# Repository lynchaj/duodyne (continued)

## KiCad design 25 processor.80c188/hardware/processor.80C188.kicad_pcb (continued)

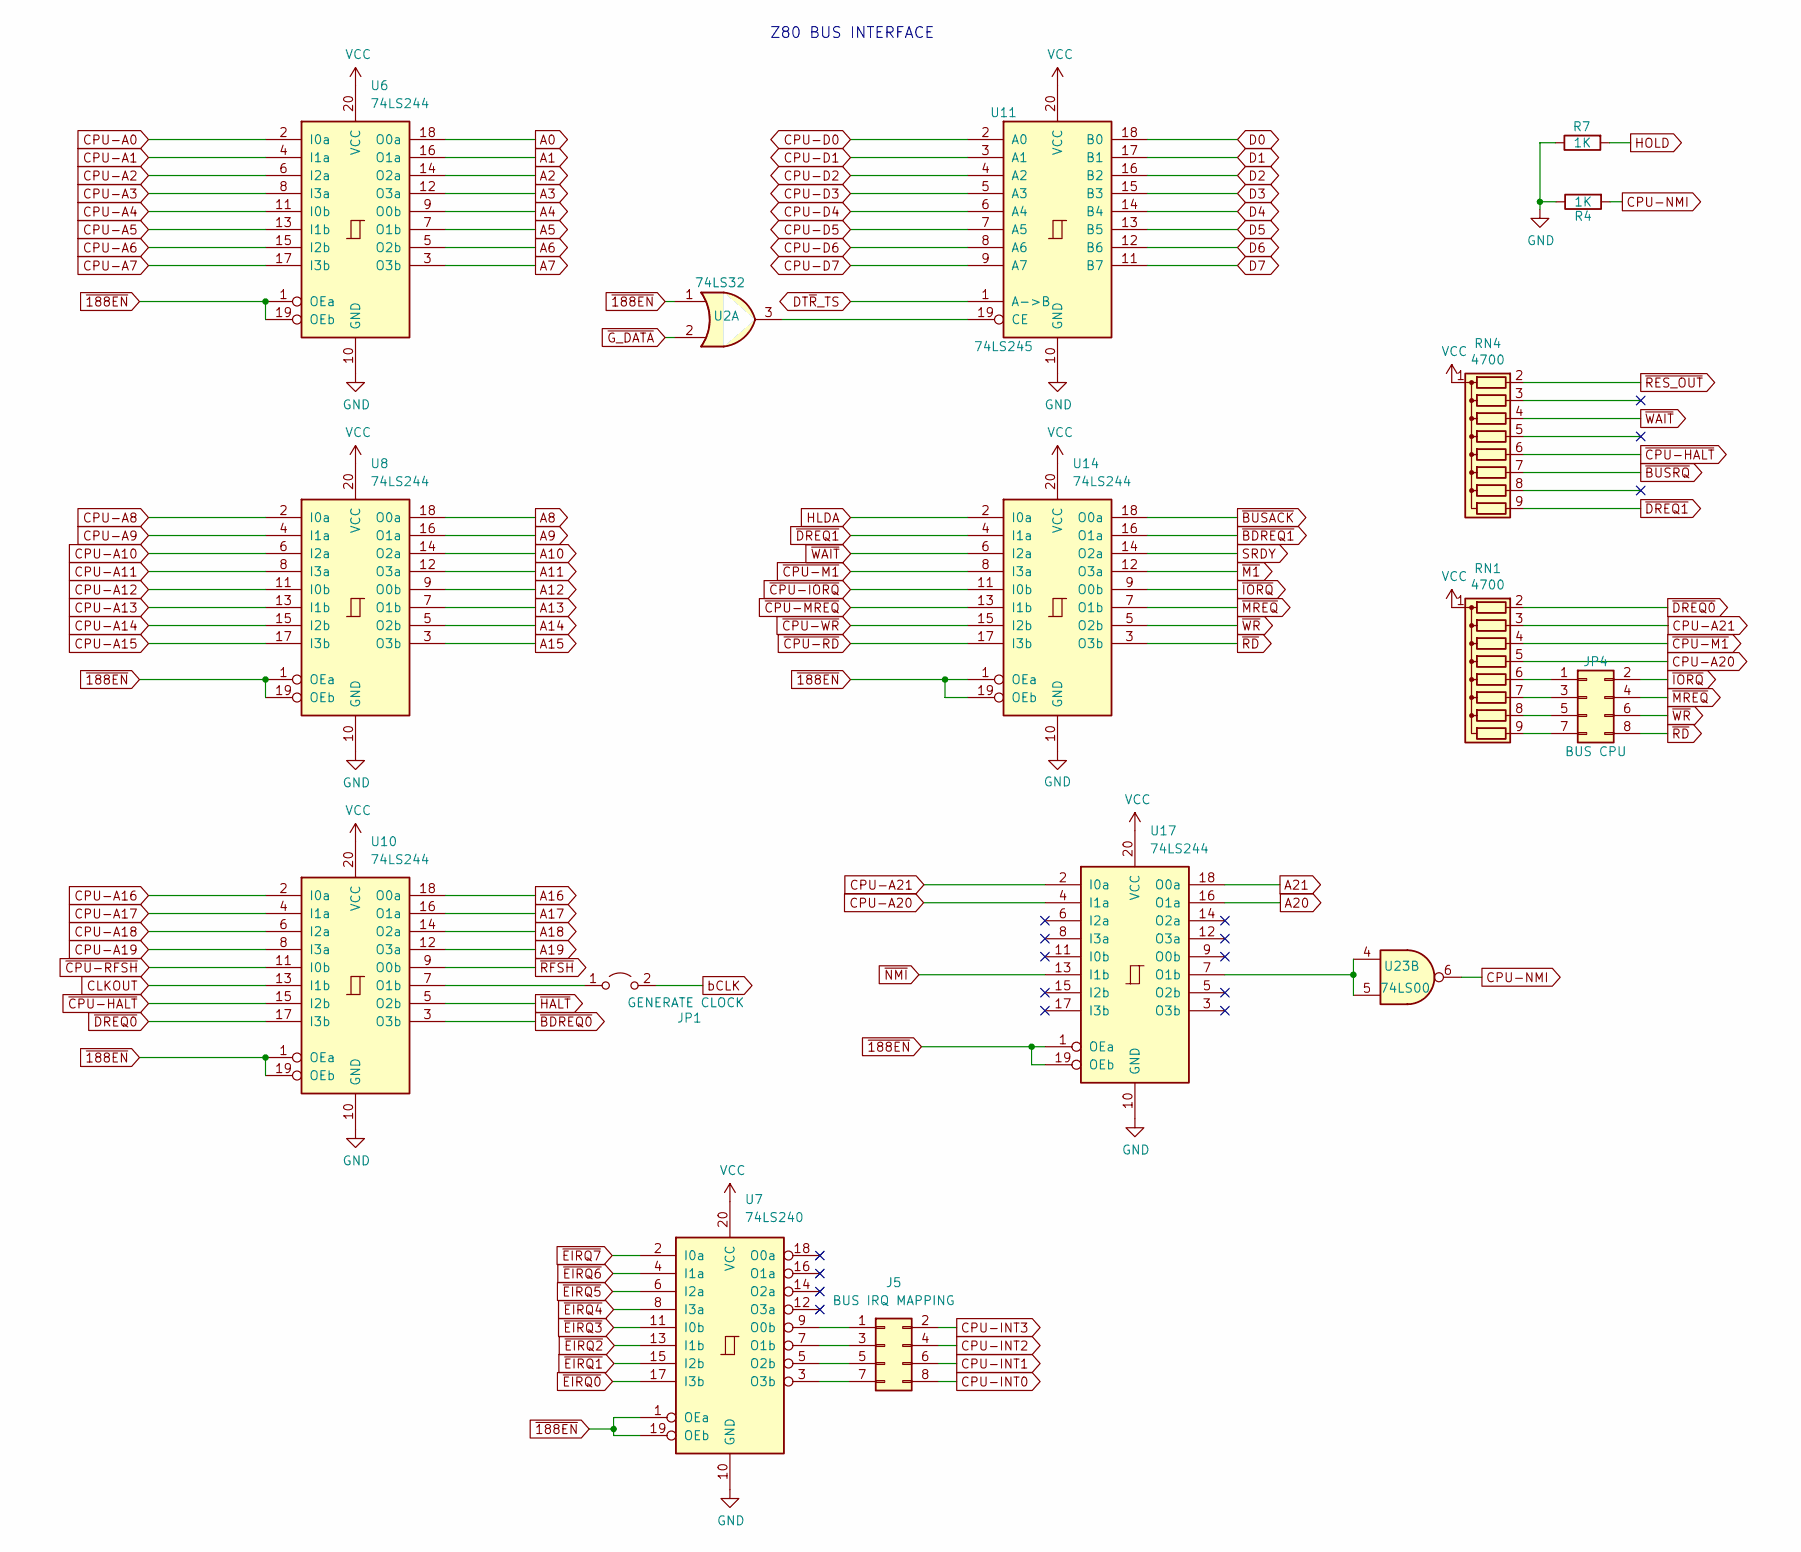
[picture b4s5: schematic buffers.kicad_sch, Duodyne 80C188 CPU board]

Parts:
J5: BUS IRQ MAPPING; PinHeader_2x04_P2.54mm_Vertical
JP1: GENERATE CLOCK; PinHeader_1x02_P2.54mm_Vertical
JP4: BUS CPU; PinHeader_2x04_P2.54mm_Vertical
R4, R7: 1K; R_Axial_DIN0207_L6.3mm_D2.5mm_P7.62mm_Horizontal
RN1, RN4: 4700; R_Array_SIP9
U2: 74LS32; DIP-14_W7.62mm_Socket_LongPads
U6, U8, U10, U14, U17: 74LS244; DIP-20_W7.62mm_Socket_LongPads
U7: 74LS240; DIP-20_W7.62mm_Socket_LongPads
U11: 74LS245; DIP-20_W7.62mm_Socket_LongPads
U23: 74LS00; DIP-14_W7.62mm_Socket_LongPads

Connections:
A0: U6.18 (O0a); also elsewhere on the board
A1: U6.16 (O1a); also elsewhere on the board
A2: U6.14 (O2a); also elsewhere on the board
A3: U6.12 (O3a); also elsewhere on the board
A4: U6.9 (O0b); also elsewhere on the board
A5: U6.7 (O1b); also elsewhere on the board
A6: U6.5 (O2b); also elsewhere on the board
A7: U6.3 (O3b); also elsewhere on the board
A8: U8.18 (O0a); also elsewhere on the board
A9: U8.16 (O1a); also elsewhere on the board
A10: U8.14 (O2a); also elsewhere on the board
A11: U8.12 (O3a); also elsewhere on the board
A12: U8.9 (O0b); also elsewhere on the board
A13: U8.7 (O1b); also elsewhere on the board
A14: U8.5 (O2b); also elsewhere on the board
A15: U8.3 (O3b); also elsewhere on the board
A16: U10.18 (O0a); also elsewhere on the board
A17: U10.16 (O1a); also elsewhere on the board
A18: U10.14 (O2a); also elsewhere on the board
A19: U10.12 (O3a); also elsewhere on the board
A20: U17.16 (O1a); also elsewhere on the board
A21: U17.18 (O0a); also elsewhere on the board
CLKOUT: U10.13 (I1b); also elsewhere on the board
CPU-A0: U6.2 (I0a); also elsewhere on the board
CPU-A1: U6.4 (I1a); also elsewhere on the board
CPU-A2: U6.6 (I2a); also elsewhere on the board
CPU-A3: U6.8 (I3a); also elsewhere on the board
CPU-A4: U6.11 (I0b); also elsewhere on the board
CPU-A5: U6.13 (I1b); also elsewhere on the board
CPU-A6: U6.15 (I2b); also elsewhere on the board
CPU-A7: U6.17 (I3b); also elsewhere on the board
CPU-A8: U8.2 (I0a); also elsewhere on the board
CPU-A9: U8.4 (I1a); also elsewhere on the board
CPU-A10: U8.6 (I2a); also elsewhere on the board
CPU-A11: U8.8 (I3a); also elsewhere on the board
CPU-A12: U8.11 (I0b); also elsewhere on the board
CPU-A13: U8.13 (I1b); also elsewhere on the board
CPU-A14: U8.15 (I2b); also elsewhere on the board
CPU-A15: U8.17 (I3b); also elsewhere on the board
CPU-A16: U10.2 (I0a); also elsewhere on the board
CPU-A17: U10.4 (I1a); also elsewhere on the board
CPU-A18: U10.6 (I2a); also elsewhere on the board
CPU-A19: U10.8 (I3a); also elsewhere on the board
CPU-A20: RN1.5 (R4), U17.4 (I1a)
CPU-A21: RN1.3 (R2), U17.2 (I0a)
CPU-D0: U11.2 (A0); also elsewhere on the board
CPU-D1: U11.3 (A1); also elsewhere on the board
CPU-D2: U11.4 (A2); also elsewhere on the board
CPU-D3: U11.5 (A3); also elsewhere on the board
CPU-D4: U11.6 (A4); also elsewhere on the board
CPU-D5: U11.7 (A5); also elsewhere on the board
CPU-D6: U11.8 (A6); also elsewhere on the board
CPU-D7: U11.9 (A7); also elsewhere on the board
CPU-INT0: J5.8; also elsewhere on the board
CPU-INT1: J5.6; also elsewhere on the board
CPU-INT2: J5.4; also elsewhere on the board
CPU-INT3: J5.2; also elsewhere on the board
CPU-NMI: R4.2, U23.6; also elsewhere on the board
D0: U11.18 (B0); also elsewhere on the board
D1: U11.17 (B1); also elsewhere on the board
D2: U11.16 (B2); also elsewhere on the board
D3: U11.15 (B3); also elsewhere on the board
D4: U11.14 (B4); also elsewhere on the board
D5: U11.13 (B5); also elsewhere on the board
D6: U11.12 (B6); also elsewhere on the board
D7: U11.11 (B7); also elsewhere on the board
DT~R_TS: U11.1 (A->B); also elsewhere on the board
GND: R4.1, R7.1, U6.10 (GND), U7.10 (GND), U8.10 (GND), U10.10 (GND), U11.10 (GND), U14.10 (GND), U17.10 (GND); also elsewhere on the board
HLDA: U14.2 (I0a); also elsewhere on the board
HOLD: R7.2; also elsewhere on the board
unnamed: J5.1, U7.9 (O0b)
unnamed: J5.3, U7.7 (O1b)
unnamed: J5.5, U7.5 (O2b)
unnamed: J5.7, U7.3 (O3b)
unnamed: JP1.1 (A), U10.7 (O1b)
unnamed: JP4.1, RN1.6 (R5)
unnamed: JP4.3, RN1.7 (R6)
unnamed: JP4.5, RN1.8 (R7)
unnamed: JP4.7, RN1.9 (R8)
unnamed: U2.3, U11.19 (CE)
unnamed: U17.7 (O1b), U23.4, U23.5
SRDY: U14.14 (O2a); also elsewhere on the board
VCC: RN1.1 (common), RN4.1 (common), U6.20 (VCC), U7.20 (VCC), U8.20 (VCC), U10.20 (VCC), U11.20 (VCC), U14.20 (VCC), U17.20 (VCC); also elsewhere on the board
bCLK: JP1.2 (B); also elsewhere on the board
~188EN: U2.1, U6.1 (OEa), U6.19 (OEb), U7.1 (OEa), U7.19 (OEb), U8.1 (OEa), U8.19 (OEb), U10.1 (OEa), U10.19 (OEb), U14.1 (OEa), U14.19 (OEb), U17.1 (OEa), U17.19 (OEb); also elsewhere on the board
~BDREQ0: U10.3 (O3b); also elsewhere on the board
~BDREQ1: U14.16 (O1a); also elsewhere on the board
~BUSACK: U14.18 (O0a); also elsewhere on the board
~BUSRQ: RN4.7 (R6); also elsewhere on the board
~CPU-HALT: RN4.6 (R5), U10.15 (I2b); also elsewhere on the board
~CPU-IORQ: U14.11 (I0b); also elsewhere on the board
~CPU-M1: RN1.4 (R3), U14.8 (I3a); also elsewhere on the board
~CPU-MREQ: U14.13 (I1b); also elsewhere on the board
~CPU-RD: U14.17 (I3b); also elsewhere on the board
~CPU-RFSH: U10.11 (I0b); also elsewhere on the board
~CPU-WR: U14.15 (I2b); also elsewhere on the board
~DREQ0: RN1.2 (R1), U10.17 (I3b); also elsewhere on the board
~DREQ1: RN4.9 (R8), U14.4 (I1a); also elsewhere on the board
~EIRQ0: U7.17 (I3b); also elsewhere on the board
~EIRQ1: U7.15 (I2b); also elsewhere on the board
~EIRQ2: U7.13 (I1b); also elsewhere on the board
~EIRQ3: U7.11 (I0b); also elsewhere on the board
~EIRQ4: U7.8 (I3a); also elsewhere on the board
~EIRQ5: U7.6 (I2a); also elsewhere on the board
~EIRQ6: U7.4 (I1a); also elsewhere on the board
~EIRQ7: U7.2 (I0a); also elsewhere on the board
~G_DATA: U2.2; also elsewhere on the board
~HALT: U10.5 (O2b); also elsewhere on the board
~IORQ: JP4.2, U14.9 (O0b); also elsewhere on the board
~M1: U14.12 (O3a); also elsewhere on the board
~MREQ: JP4.4, U14.7 (O1b); also elsewhere on the board
~NMI: U17.13 (I1b); also elsewhere on the board
~RD: JP4.8, U14.3 (O3b); also elsewhere on the board
~RES_OUT: RN4.2 (R1); also elsewhere on the board
~RFSH: U10.9 (O0b); also elsewhere on the board
~WAIT: RN4.4 (R3), U14.6 (I2a); also elsewhere on the board
~WR: JP4.6, U14.5 (O2b); also elsewhere on the board

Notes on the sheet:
Z80 BUS INTERFACE

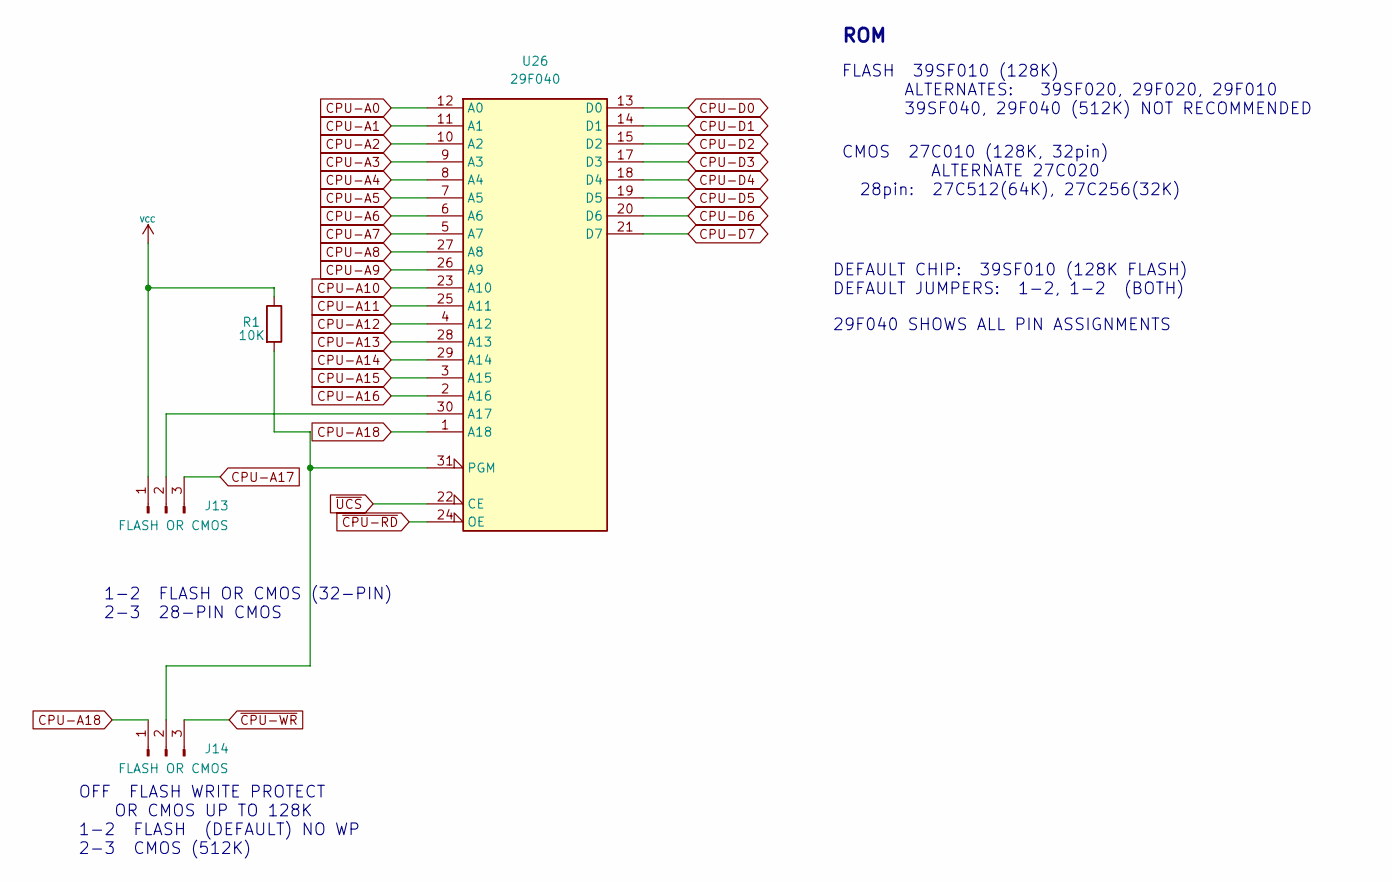
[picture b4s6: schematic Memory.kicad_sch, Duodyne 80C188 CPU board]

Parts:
J13, J14: FLASH OR CMOS; PinHeader_1x03_P2.54mm_Vertical
R1: 10K; R_Axial_DIN0207_L6.3mm_D2.5mm_P7.62mm_Horizontal
U26: 29F040; DIP-32_W15.24mm_Socket_LongPads

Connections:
CPU-A0: U26.12 (A0); also elsewhere on the board
CPU-A1: U26.11 (A1); also elsewhere on the board
CPU-A2: U26.10 (A2); also elsewhere on the board
CPU-A3: U26.9 (A3); also elsewhere on the board
CPU-A4: U26.8 (A4); also elsewhere on the board
CPU-A5: U26.7 (A5); also elsewhere on the board
CPU-A6: U26.6 (A6); also elsewhere on the board
CPU-A7: U26.5 (A7); also elsewhere on the board
CPU-A8: U26.27 (A8); also elsewhere on the board
CPU-A9: U26.26 (A9); also elsewhere on the board
CPU-A10: U26.23 (A10); also elsewhere on the board
CPU-A11: U26.25 (A11); also elsewhere on the board
CPU-A12: U26.4 (A12); also elsewhere on the board
CPU-A13: U26.28 (A13); also elsewhere on the board
CPU-A14: U26.29 (A14); also elsewhere on the board
CPU-A15: U26.3 (A15); also elsewhere on the board
CPU-A16: U26.2 (A16); also elsewhere on the board
CPU-A17: J13.3; also elsewhere on the board
CPU-A18: J14.1, U26.1 (A18); also elsewhere on the board
CPU-D0: U26.13 (D0); also elsewhere on the board
CPU-D1: U26.14 (D1); also elsewhere on the board
CPU-D2: U26.15 (D2); also elsewhere on the board
CPU-D3: U26.17 (D3); also elsewhere on the board
CPU-D4: U26.18 (D4); also elsewhere on the board
CPU-D5: U26.19 (D5); also elsewhere on the board
CPU-D6: U26.20 (D6); also elsewhere on the board
CPU-D7: U26.21 (D7); also elsewhere on the board
GND: U26.16 (GND); also elsewhere on the board
unnamed: J13.2, U26.30 (A17)
unnamed: J14.2, R1.2, U26.31 (PGM)
VCC: J13.1, R1.1, U26.32 (VCC); also elsewhere on the board
~CPU-RD: U26.24 (OE); also elsewhere on the board
~CPU-WR: J14.3; also elsewhere on the board
~UCS: U26.22 (CE); also elsewhere on the board

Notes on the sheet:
29F040 SHOWS ALL PIN ASSIGNMENTS
CMOS 27C010 (128K, 32pin) ALTERNATE 27C020 28pin: 27C512(64K), 27C256(32K)
ROM
FLASH 39SF010 (128K) ALTERNATES: 39SF020, 29F020, 29F010 39SF040, 29F040 (512K) NOT RECOMMENDED
1-2 FLASH OR CMOS (32-PIN) 2-3 28-PIN CMOS
DEFAULT CHIP: 39SF010 (128K FLASH) DEFAULT JUMPERS: 1-2, 1-2 (BOTH)
OFF FLASH WRITE PROTECT OR CMOS UP TO 128K 1-2 FLASH (DEFAULT) NO WP 2-3 CMOS (512K)

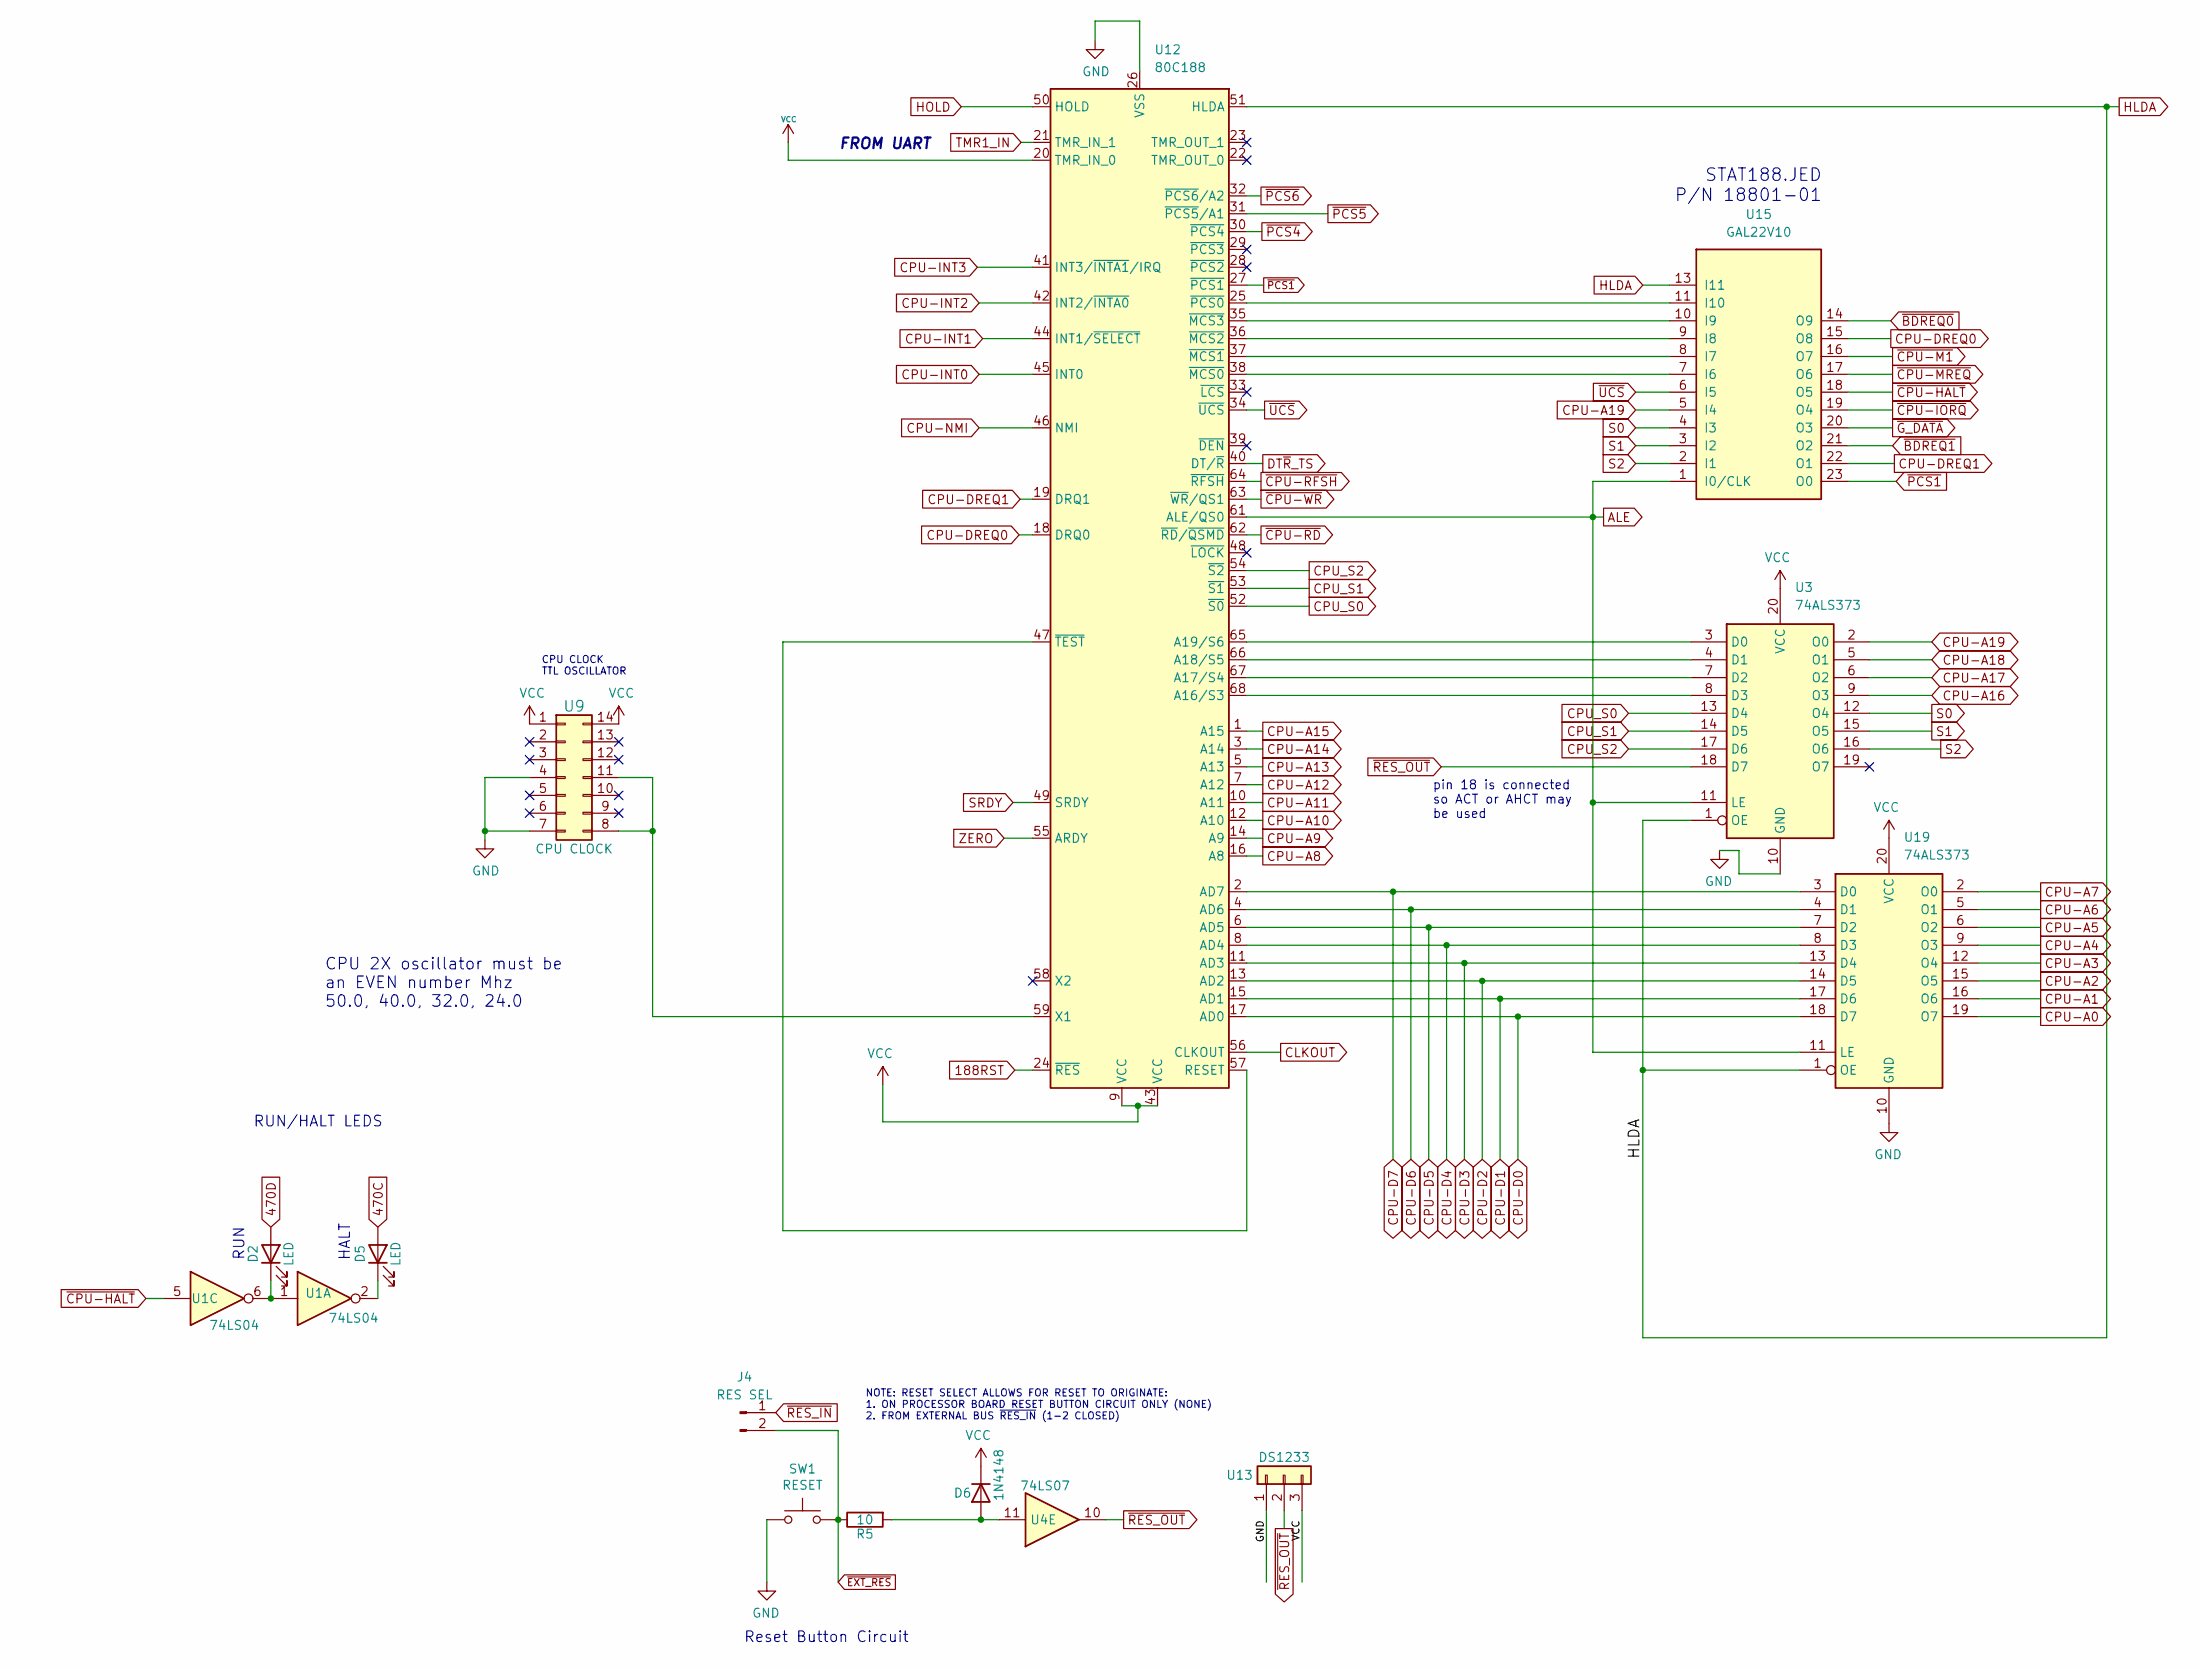
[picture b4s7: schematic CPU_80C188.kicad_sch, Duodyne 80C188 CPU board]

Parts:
D2, D5: LED; LED_D3.0mm_Horizontal_O3.81mm_Z2.0mm
D6: 1N4148; D_DO-35_SOD27_P7.62mm_Horizontal
J4: RES SEL; PinHeader_1x02_P2.54mm_Vertical
R5: 10; R_Axial_DIN0207_L6.3mm_D2.5mm_P7.62mm_Horizontal
SW1: RESET; SW_Tactile_SPST_Angled_PTS645Vx58-2LFS
U1: 74LS04; DIP-14_W7.62mm_Socket_LongPads
U3, U19: 74ALS373; DIP-20_W7.62mm_Socket_LongPads
U4: 74LS07; DIP-14_W7.62mm_Socket_LongPads
U9: CPU CLOCK; DIP-14_W7.62mm_Socket_LongPads
U12: 80C188; 80C188_52
U13: DS1233; TO-92L_HandSolder
U15: GAL22V10; DIP-24_W7.62mm_Socket_LongPads

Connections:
188RST: U12.24 (~RES); also elsewhere on the board
470C: D5.2 (A); also elsewhere on the board
470D: D2.2 (A); also elsewhere on the board
ALE: U3.11 (LE), U12.61 (ALE/QS0), U15.1 (I0/CLK), U19.11 (LE); also elsewhere on the board
CLKOUT: U12.56 (CLKOUT); also elsewhere on the board
CPU-A0: U19.19 (O7); also elsewhere on the board
CPU-A1: U19.16 (O6); also elsewhere on the board
CPU-A2: U19.15 (O5); also elsewhere on the board
CPU-A3: U19.12 (O4); also elsewhere on the board
CPU-A4: U19.9 (O3); also elsewhere on the board
CPU-A5: U19.6 (O2); also elsewhere on the board
CPU-A6: U19.5 (O1); also elsewhere on the board
CPU-A7: U19.2 (O0); also elsewhere on the board
CPU-A8: U12.16 (A8); also elsewhere on the board
CPU-A9: U12.14 (A9); also elsewhere on the board
CPU-A10: U12.12 (A10); also elsewhere on the board
CPU-A11: U12.10 (A11); also elsewhere on the board
CPU-A12: U12.7 (A12); also elsewhere on the board
CPU-A13: U12.5 (A13); also elsewhere on the board
CPU-A14: U12.3 (A14); also elsewhere on the board
CPU-A15: U12.1 (A15); also elsewhere on the board
CPU-A16: U3.9 (O3); also elsewhere on the board
CPU-A17: U3.6 (O2); also elsewhere on the board
CPU-A18: U3.5 (O1); also elsewhere on the board
CPU-A19: U3.2 (O0), U15.5 (I4); also elsewhere on the board
CPU-D0: U12.17 (AD0), U19.18 (D7); also elsewhere on the board
CPU-D1: U12.15 (AD1), U19.17 (D6); also elsewhere on the board
CPU-D2: U12.13 (AD2), U19.14 (D5); also elsewhere on the board
CPU-D3: U12.11 (AD3), U19.13 (D4); also elsewhere on the board
CPU-D4: U12.8 (AD4), U19.8 (D3); also elsewhere on the board
CPU-D5: U12.6 (AD5), U19.7 (D2); also elsewhere on the board
CPU-D6: U12.4 (AD6), U19.4 (D1); also elsewhere on the board
CPU-D7: U12.2 (AD7), U19.3 (D0); also elsewhere on the board
CPU-DREQ0: U12.18 (DRQ0), U15.15 (O8)
CPU-DREQ1: U12.19 (DRQ1), U15.22 (O1)
CPU-INT0: U12.45 (INT0); also elsewhere on the board
CPU-INT1: U12.44 (INT1/~SELECT); also elsewhere on the board
CPU-INT2: U12.42 (INT2/~INTA0); also elsewhere on the board
CPU-INT3: U12.41 (INT3/~INTA1/IRQ); also elsewhere on the board
CPU-NMI: U12.46 (NMI); also elsewhere on the board
CPU_S0: U3.13 (D4), U12.52 (~S0)
CPU_S1: U3.14 (D5), U12.53 (~S1)
CPU_S2: U3.17 (D6), U12.54 (~S2)
DT~R_TS: U12.40 (DT/~R); also elsewhere on the board
GND: SW1.2, U3.10 (GND), U9.4, U9.7, U12.26 (VSS), U12.60 (VSS), U13.1, U15.12 (GND), U19.10 (GND); also elsewhere on the board
HLDA: U3.1 (OE), U12.51 (HLDA), U15.13 (I11), U19.1 (OE); also elsewhere on the board
HOLD: U12.50 (HOLD); also elsewhere on the board
unnamed: D2.1 (K), U1.1, U1.6
unnamed: D5.1 (K), U1.2
unnamed: D6.2 (A), R5.2, U4.11
unnamed: U12.25 (~PCS0), U15.11 (I10)
unnamed: U12.35 (~MCS3), U15.10 (I9)
unnamed: U12.36 (~MCS2), U15.9 (I8)
unnamed: U12.37 (~MCS1), U15.8 (I7)
unnamed: U12.38 (~MCS0), U15.7 (I6)
unnamed: U12.47 (~TEST), U12.57 (RESET)
unnamed: U9.8, U9.11, U12.59 (X1)
unnamed: U3.3 (D0), U12.65 (A19/S6)
unnamed: U3.4 (D1), U12.66 (A18/S5)
unnamed: U3.7 (D2), U12.67 (A17/S4)
unnamed: U3.8 (D3), U12.68 (A16/S3)
S0: U3.12 (O4), U15.4 (I3)
S1: U3.15 (O5), U15.3 (I2)
S2: U3.16 (O6), U15.2 (I1); also elsewhere on the board
SRDY: U12.49 (SRDY); also elsewhere on the board
TMR1_IN: U12.21 (TMR_IN_1); also elsewhere on the board
VCC: D6.1 (K), U3.20 (VCC), U9.1, U9.14, U12.9 (VCC), U12.20 (TMR_IN_0), U12.43 (VCC), U13.3, U15.24 (VCC), U19.20 (VCC); also elsewhere on the board
ZERO: U12.55 (ARDY); also elsewhere on the board
~BDREQ0: U15.14 (O9); also elsewhere on the board
~BDREQ1: U15.21 (O2); also elsewhere on the board
~CPU-HALT: U1.5, U15.18 (O5); also elsewhere on the board
~CPU-IORQ: U15.19 (O4); also elsewhere on the board
~CPU-M1: U15.16 (O7); also elsewhere on the board
~CPU-MREQ: U15.17 (O6); also elsewhere on the board
~CPU-RD: U12.62 (~RD/~QSMD); also elsewhere on the board
~CPU-RFSH: U12.64 (~RFSH); also elsewhere on the board
~CPU-WR: U12.63 (~WR/QS1); also elsewhere on the board
~EXT_RES: J4.2, R5.1, SW1.1; also elsewhere on the board
~G_DATA: U15.20 (O3); also elsewhere on the board
~PCS1: U12.27 (~PCS1), U15.23 (O0)
~PCS4: U12.30 (~PCS4); also elsewhere on the board
~PCS5: U12.31 (~PCS5/A1); also elsewhere on the board
~PCS6: U12.32 (~PCS6/A2); also elsewhere on the board
~RES_IN: J4.1; also elsewhere on the board
~RES_OUT: U3.18 (D7), U4.10, U13.2; also elsewhere on the board
~UCS: U12.34 (~UCS), U15.6 (I5); also elsewhere on the board

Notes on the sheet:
pin 18 is connected so ACT or AHCT may be used
STAT188.JED P/N 18801-01
CPU CLOCK TTL OSCILLATOR
RUN
HALT
NOTE: RESET SELECT ALLOWS FOR RESET TO ORIGINATE: 1. ON PROCESSOR BOARD RESET BUTTON CIRCUIT ONLY (NONE) 2. FROM EXTERNAL BUS ~{RES_IN} (1-2 CLOSED)
FROM UART
Reset Button Circuit
CPU 2X oscillator must be an EVEN number Mhz 50.0, 40.0, 32.0, 24.0
RUN/HALT LEDS

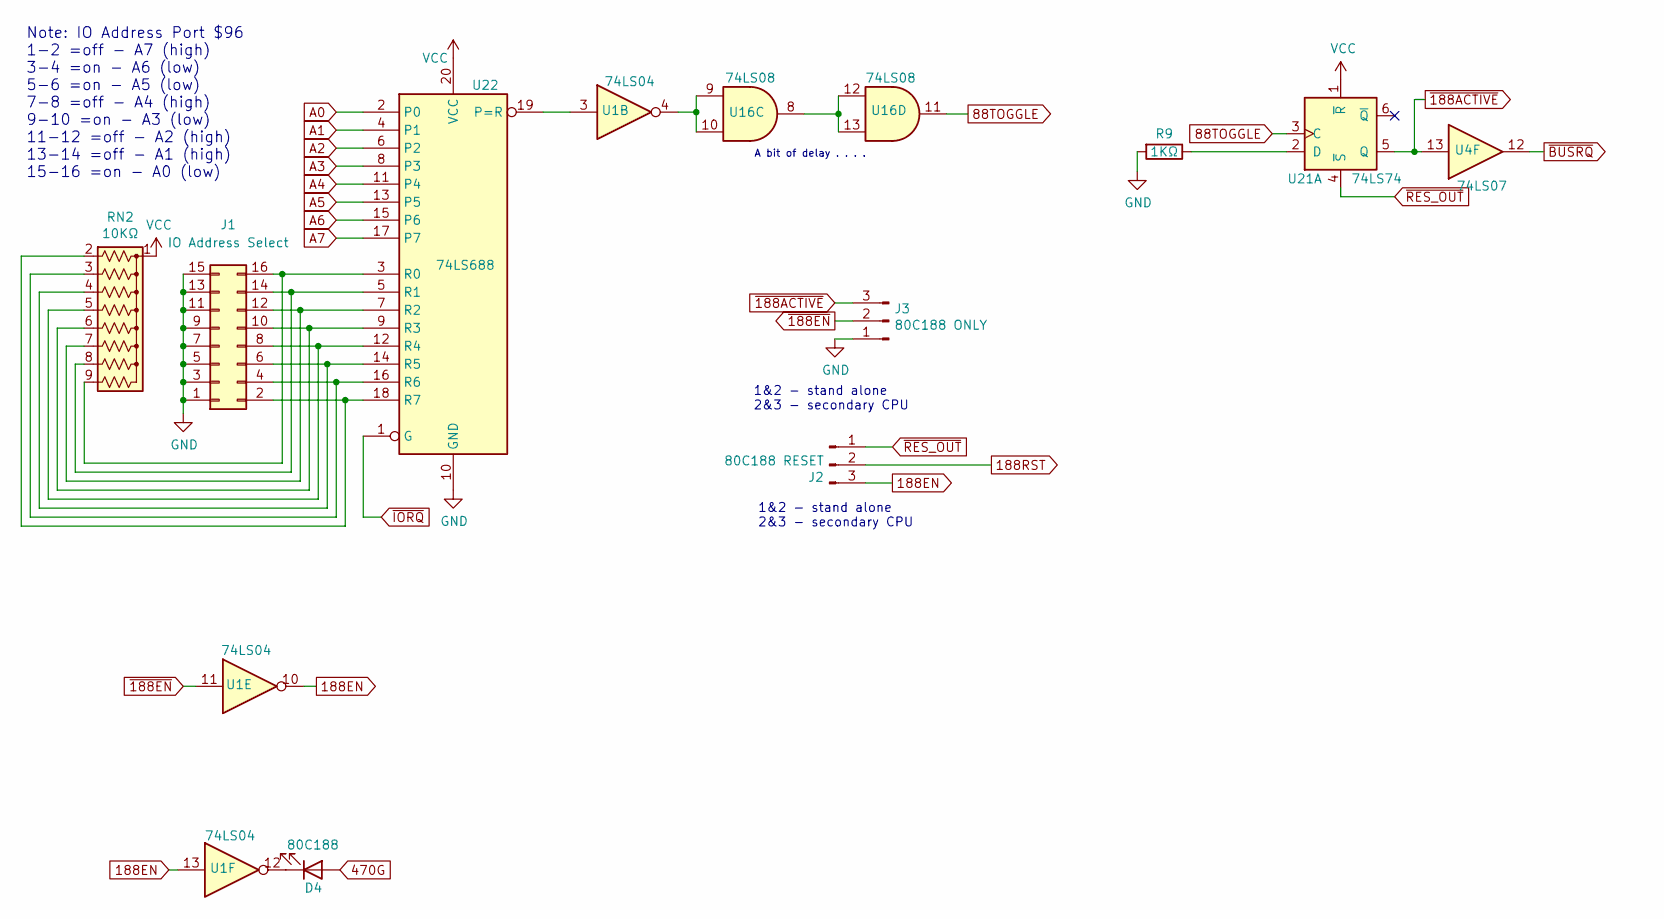
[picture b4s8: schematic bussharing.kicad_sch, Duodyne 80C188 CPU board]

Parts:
D4: 80C188; LED_D3.0mm_Horizontal_O3.81mm_Z2.0mm
J1: IO Address Select; PinHeader_2x08_P2.54mm_Vertical
J2: 80C188 RESET; PinHeader_1x03_P2.54mm_Horizontal
J3: 80C188 ONLY; PinHeader_1x03_P2.54mm_Horizontal
R9: 1KΩ; R_Axial_DIN0207_L6.3mm_D2.5mm_P7.62mm_Horizontal
RN2: 10KΩ; R_Array_SIP9
U1: 74LS04; DIP-14_W7.62mm_Socket_LongPads
U4: 74LS07; DIP-14_W7.62mm_Socket_LongPads
U16: 74LS08; DIP-14_W7.62mm_Socket_LongPads
U21: 74LS74; DIP-14_W7.62mm_Socket_LongPads
U22: 74LS688; DIP-20_W7.62mm_Socket_LongPads

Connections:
88TOGGLE: U16.11, U21.3 (C)
188EN: J2.3, U1.10, U1.13
188RST: J2.2; also elsewhere on the board
470G: D4.2 (A); also elsewhere on the board
A0: U22.2 (P0); also elsewhere on the board
A1: U22.4 (P1); also elsewhere on the board
A2: U22.6 (P2); also elsewhere on the board
A3: U22.8 (P3); also elsewhere on the board
A4: U22.11 (P4); also elsewhere on the board
A5: U22.13 (P5); also elsewhere on the board
A6: U22.15 (P6); also elsewhere on the board
A7: U22.17 (P7); also elsewhere on the board
GND: J1.1, J1.3, J1.5, J1.7, J1.9, J1.11, J1.13, J1.15, J3.1, R9.2, U22.10 (GND); also elsewhere on the board
unnamed: D4.1 (K), U1.12
unnamed: J1.2, RN2.2 (R1), U22.18 (R7)
unnamed: J1.4, RN2.3 (R2), U22.16 (R6)
unnamed: J1.6, RN2.4 (R3), U22.14 (R5)
unnamed: J1.8, RN2.5 (R4), U22.12 (R4)
unnamed: J1.10, RN2.6 (R5), U22.9 (R3)
unnamed: J1.12, RN2.7 (R6), U22.7 (R2)
unnamed: J1.14, RN2.8 (R7), U22.5 (R1)
unnamed: J1.16, RN2.9 (R8), U22.3 (R0)
unnamed: R9.1, U21.2 (D)
unnamed: U1.3, U22.19 (P=R)
unnamed: U1.4, U16.9, U16.10
unnamed: U16.8, U16.12, U16.13
VCC: RN2.1 (common), U21.1 (~R), U22.20 (VCC); also elsewhere on the board
~188ACTIVE: J3.3, U4.13, U21.5 (Q)
~188EN: J3.2, U1.11; also elsewhere on the board
~BUSRQ: U4.12; also elsewhere on the board
~IORQ: U22.1 (G); also elsewhere on the board
~RES_OUT: J2.1, U21.4 (~S); also elsewhere on the board

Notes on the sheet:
1&2 - stand alone 2&3 - secondary CPU
A bit of delay . . . .
Note: IO Address Port $96 1-2 =off - A7 (high) 3-4 =on - A6 (low) 5-6 =on - A5 (low) 7-8 =off - A4 (high) 9-10 =on - A3 (low) 11-12 =off - A2 (high) 13-14 =off - A1 (high) 15-16 =on - A0 (low)

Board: 2 copper layers, 111 parts (0 on the bottom side), 224 nets, no tracks yet.

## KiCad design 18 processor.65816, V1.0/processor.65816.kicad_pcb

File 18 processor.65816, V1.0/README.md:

# 65C816 CPU Card
68C816 processor board (hardware and software) for the Duodyne computer system.

The board contains:
* 65C816 CPU (up to 4Mhz)
* 8K Rom (the first 8K of the EPROM)
* Support for a Standard Duodyne Front Panel
* 16c550 UART

IO is mapped from $00DF00 - $00DF00 for boards prior to V1.31 and is mapped at $xx0300-$xx03FF for 1.31 and later
The on-board ROM is mapped from 00E000-00FFFF.

On board IO Address Port $50-$5F
$50	     Front Panel (RW)
$51	     Option Latch (bit 0, enable interrups, bits 1-7 exposed on front panel connector)
$52	     
$53	     Reset
$54          
$55      
$56
$57 
$58-$5F UART (RW)

Rom Images are in this repo.   DOS/65 operating system sources and images can be found here: https://github.com/danwerner21/6x0x-DOS65
DOS/65 does not work on boards prior to V1.31

# Jumper Settings
        JP1  - Allow RES_IN to generate board Reset

        J2  - Reset Control
                1&2 Only CPU
                2&3 Secondary CPU
                
        J3  - CPU Control
                1&2 Only CPU
                2&3 Secondary CPU

        JP3 - Generate Clock
                OPEN Does not place CPU Clock on BUS
                CLOSED Places CPU Clock on BUS

        JP4 - Reset
                OPEN Does not Connect RES_OUT to BUS
                CLOSED Connect RES_OUT to BUS

        JP10  - IO ADDRESS Select
        JP13  - UART IRQ Enable

# Bugs

Note that the PCF8584 I2C bus controller has been removed from the design after V1.3 as it never worked reliably. The timing requirements of the chip are just too different from what the 65816 is capible of delivering and the work arounds are honestly more trouble than the functionality is worth (IMHO).  

V1.2
* Activation Flip flop needs reset by RES_OUT rather then RES_IN.   Easiest patch is to connect RES_IN to RES_OUT-  JP1 pin 1 to U15 pin 2 (once done DO NOT JUMPER JP1)
* cut connection between JP1 pin 1 and P1 pin 20
* Do not populate U27, U28, R2, R3, and JP2

V1.3
* R15 incorrectly ties M1 to GND.  Do not populate the GND side of this resistor, but instead solder that side to the nearest VCC pin.
* Do not populate U27, U28, R2, R3, and JP2
* U26 lift pin 3 and short pins 2 & 3 -- then use V1.31 GALs and ROMS

# BOM (V1.31)

Qty|Reference(s)|Value
--- | ----------- | -----
1|34|C1, C2, C3, C4, C5, C6, C8, C9, C10, C11, C12, C13, C14, C15, C16, C17, C18, C19, C20, C21, C22, C23, C24, C30, C31, C32, C33, C34, C35, C36, C37, C38, C39, C40|0.1uF
2|4|C25, C26, C27, C28|10uF
3|1|C29|22uF
4|1|C46|47uF
5|1|D1|BI COLOR LED
6|6|D2, D3, D5, D7, D8, D9|LED
7|1|D4|6502
8|1|D6|1N4148
10|1|IC1|65816CPU-DIP
11|1|J1|Connector_Generic:Conn_02x08_Odd_Even
12|1|J2|Connector:Conn_01x03_Male
13|1|J3|Connector:Conn_01x03_Male
14|1|J11|Pin Header Male 02x20 Right Angle| Shrouded
15|1|JP1|Connector:Conn_01x02_Male
16|1|JP3|Jumper:Jumper_2_Open
17|1|JP4|Jumper:Jumper_2_Open
18|1|JP7|Connector_Generic:Conn_02x04_Odd_Even
19|1|JP10|Connector_Generic:Conn_02x04_Odd_Even
20|1|JP13|Jumper:Jumper_2_Open
21|3|P1, P2, P3|Pin Header Male 02x25 Right Angle| Shrouded
22|7|R1, R4, R5, R6, R11, R12, R13|470 ohm
23|1|R7|10 ohm
24|1|R8|470 ohm
25|1|R9|3K ohm
26|1|R10|1K ohm
27|1|R14|100 ohm
28|1|R15|1K ohm
29|3|RN1, RN4, RN5|4700 ohm bussed  9 pin
30|1|RN2|1K  ohm bussed  9 pin
31|1|RN8|10K  ohm bussed  9 pin
32|1|SW1|Switch:SW_Push
33|6|U1, U5, U6, U11, U23, U31|74LS244
34|1|U2|UART CLOCK
35|1|U3|74LS14
36|1|U4|74LS07
37|1|U7|74LS04
38|1|U8|74LS245
39|1|U9|GAL22V10
40|1|U10|GAL16V8
41|2|U12, U22|74LS688
42|1|U13|CPU CLOCK
43|1|U14|TL16C550CFN
44|1|U15|DS1233
45|1|U16|74LS08
46|1|U17|74LS00
47|1|U18|74HC245
48|1|U19|27C64
49|1|U20|GAL22V10
50|1|U21|74LS74
51|1|U24|74HC573
52|2|U25, U33|74LS374
53|1|U26|74LS32

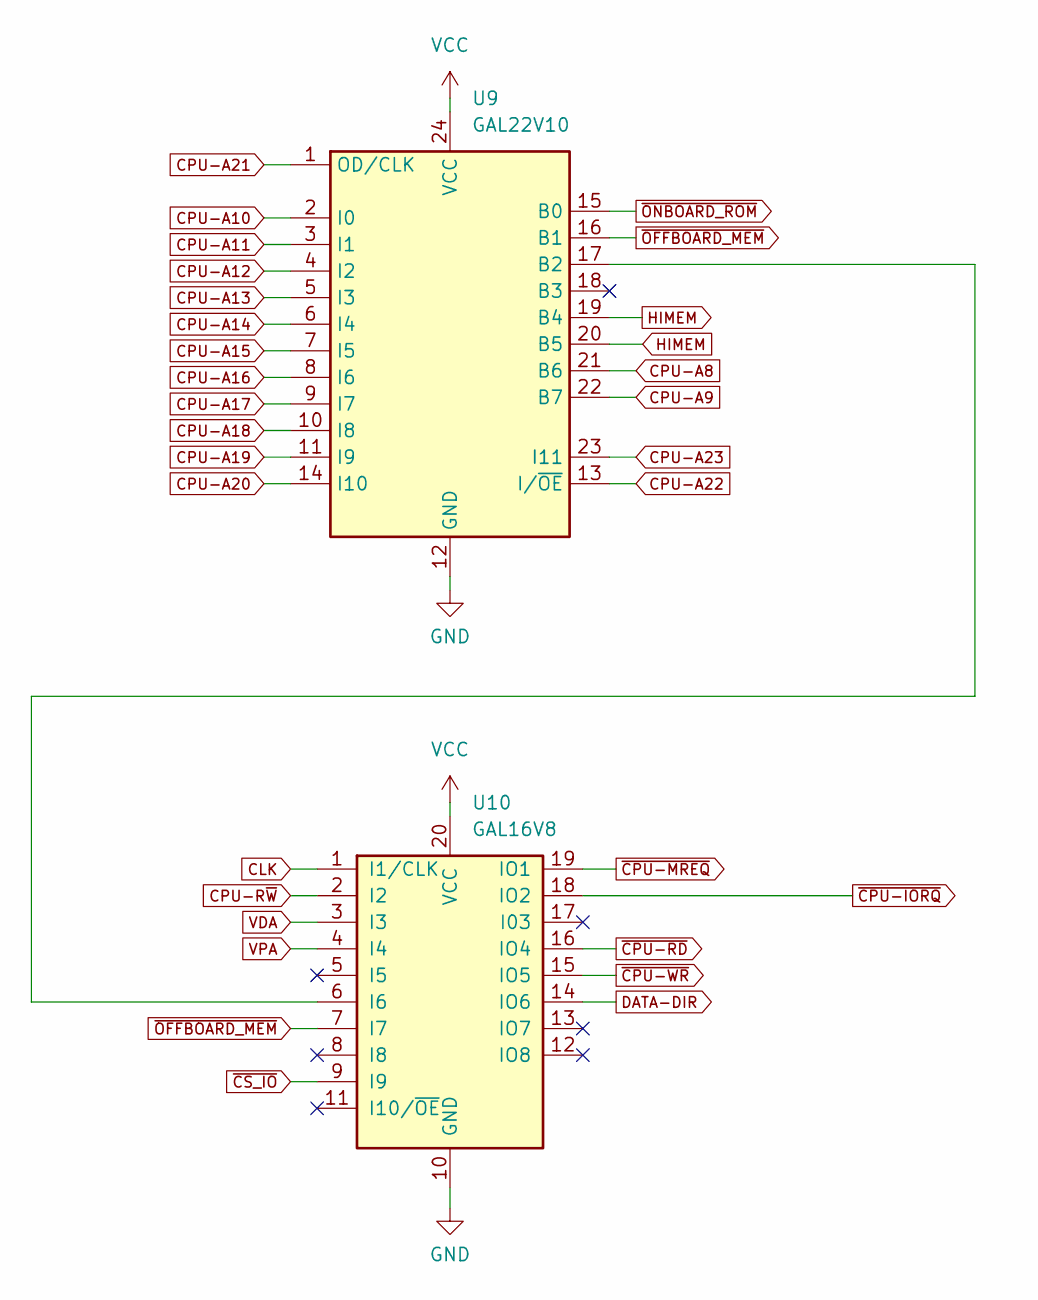
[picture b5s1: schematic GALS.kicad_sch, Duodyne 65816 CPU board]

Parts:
U9: GAL22V10; DIP-24_W7.62mm_Socket_LongPads
U10: GAL16V8; DIP-20_W7.62mm_Socket_LongPads

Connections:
CLK: U10.1 (I1/CLK); also elsewhere on the board
CPU-A8: U9.21 (B6); also elsewhere on the board
CPU-A9: U9.22 (B7); also elsewhere on the board
CPU-A10: U9.2 (I0); also elsewhere on the board
CPU-A11: U9.3 (I1); also elsewhere on the board
CPU-A12: U9.4 (I2); also elsewhere on the board
CPU-A13: U9.5 (I3); also elsewhere on the board
CPU-A14: U9.6 (I4); also elsewhere on the board
CPU-A15: U9.7 (I5); also elsewhere on the board
CPU-A16: U9.8 (I6); also elsewhere on the board
CPU-A17: U9.9 (I7); also elsewhere on the board
CPU-A18: U9.10 (I8); also elsewhere on the board
CPU-A19: U9.11 (I9); also elsewhere on the board
CPU-A20: U9.14 (I10); also elsewhere on the board
CPU-A21: U9.1 (OD/CLK); also elsewhere on the board
CPU-A22: U9.13 (I/~OE); also elsewhere on the board
CPU-A23: U9.23 (I11); also elsewhere on the board
CPU-R~W: U10.2 (I2); also elsewhere on the board
DATA-DIR: U10.14 (IO6); also elsewhere on the board
GND: U9.12 (GND), U10.10 (GND); also elsewhere on the board
HIMEM: U9.19 (B4), U9.20 (B5)
unnamed: U9.17 (B2), U10.6 (I6)
VCC: U9.24 (VCC), U10.20 (VCC); also elsewhere on the board
VDA: U10.3 (I3); also elsewhere on the board
VPA: U10.4 (I4); also elsewhere on the board
~CPU-IORQ: U10.18 (IO2); also elsewhere on the board
~CPU-MREQ: U10.19 (IO1); also elsewhere on the board
~CPU-RD: U10.16 (IO4); also elsewhere on the board
~CPU-WR: U10.15 (IO5); also elsewhere on the board
~CS_IO: U10.9 (I9); also elsewhere on the board
~OFFBOARD_MEM: U9.16 (B1), U10.7 (I7)
~ONBOARD_ROM: U9.15 (B0); also elsewhere on the board
